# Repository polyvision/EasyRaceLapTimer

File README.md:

# EasyRaceLapTimer

EasyRaceLapTimer is a complete open source lap time tracker all-in-one solution for FPV racing quads. It supports an infrared based tracker solution which is completly open hardware and a VTX solution

What you get with EasyRaceLapTimer:

**Features:**

* host system for tracking the laps
* VTX sensoring
* IR transponders (code & schematic files for building them) with a transmitting range of 2 to 4 meters
* 63 available transponder IDs when using the project transponders
* changing the ID via a push button on the transponder, no additional programming required (started with version 0.3.1 of the transponders)
* update transponders with new code (Arduino hardware needed)
* setup guide for building your Raspberry PI host station
* the host station is also a WiFi access point to change configs etc on the fly
* monitoring mode, you can watch the stats with your mobile phones
* add your own team logo to the monitoring mode
* detailed stats about pilots and races
* sound effects for various events in a race
* TCP/IP and serial connections support for receiving lap times and commands from other time tracking systems
* export race events to PDF
* standard practice/ time trial mode
* competition mode for racing events with time penalties (satellites needed)
* automatic restarting of a race session after a specified idle time
* complete race management with heats & groups
* and much more comming soon

**Important notices**

EasyRaceLapTimer works basicly with any IR transponder, as long as you provide code for interpreting the IR pulses. Just have a look at the *ir_daemon* tool.

Be sure to use the full size of your SD card on the Raspberry PI

    sudo raspi-config

# Important information

The documentation for the project can be found in the [/docs](https://github.com/polyvision/EasyRaceLapTimer/tree/master/docs) directory.
There's also a huge [RCGroups](http://www.rcgroups.com/forums/showthread.php?t=2538917) thread with lots of answered questions, images etc.

# Version 0.6.x

You can download a SD card image for the PI of EasyRaceLapTimer on the following pages:

http://www.airbirds.de
http://www.easyracelaptimer.com

There's also an introduction video to the system.

# file structure

**/docs**
  documentation of nearly every part of the package

**/web**

the rails application

**/Arduino**

all arduino sketches

**/ir_daemon**

the cpp daemon for receiving the IR pulses

**/datasheets**

schematic files and more for transponders etc.

# Installation

fetch the source via git with the following command

    git clone git@github.com:polyvision/EasyRaceLapTimer.git

more details of each indivial package can be found in the *docs* folder

# Contributors
 * [Peter Provost](https://github.com/PProvost)
 * [Peisel](https://github.com/peisel)
 * [p3root](https://github.com/p3root)
 * [Sven Michel](https://github.com/svenmichel)
 * [bilson](https://github.com/bilson)
 
 and many more ! just add yourself if you contributed!

# license

The complete project uses the [GPL V3 license](http://www.gnu.org/licenses/gpl-3.0.de.html)

**development and sponsoring by [AirBirds](http://www.airbirds.de)**

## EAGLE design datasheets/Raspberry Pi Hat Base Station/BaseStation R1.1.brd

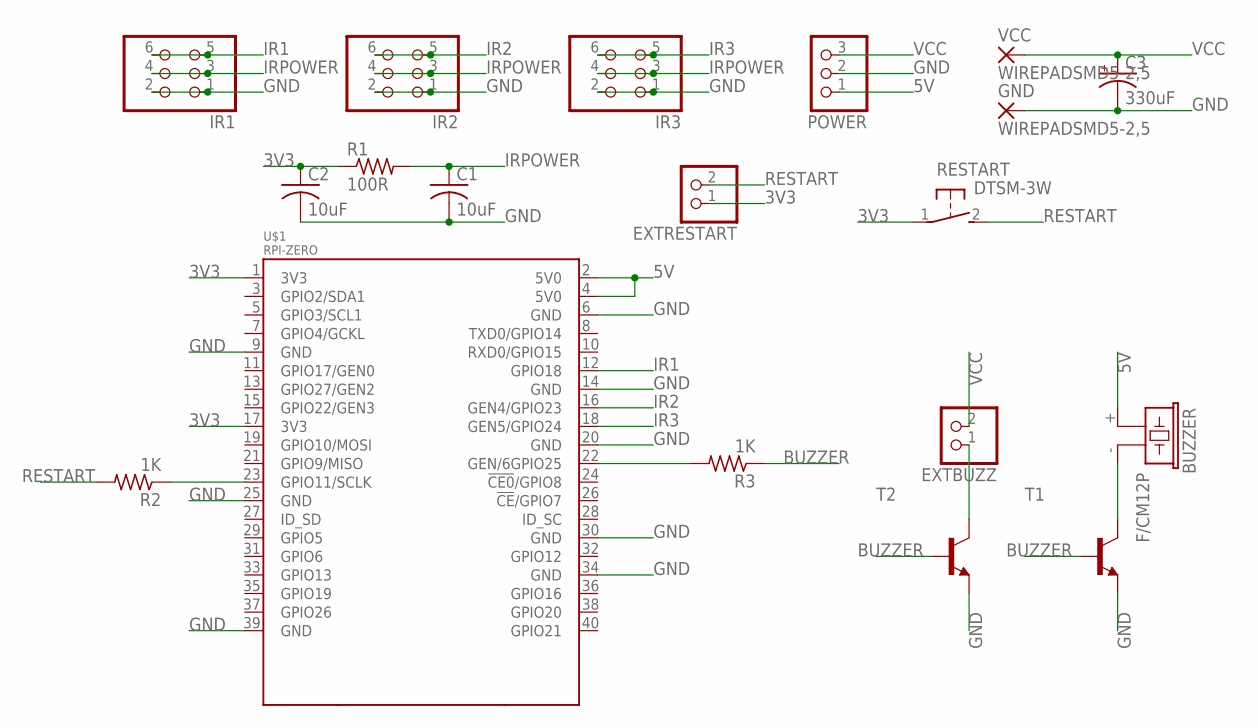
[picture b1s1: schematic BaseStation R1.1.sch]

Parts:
BUZZER: F/CM12P
C1, C2: 10uF; C1206K
C3: 330uF; E3,5-8
EXTBUZZ: PINHD-1X2; 1X02
EXTRESTART: PINHD-1X2; 1X02
GND: WIREPADSMD5-2,5; 5-2,5
IR1, IR2, IR3: PINHD-2X3; 2X03
POWER: PINHD-1X3; 1X03
R1: 100R; R1206W
R2, R3: 1K; R1206W
RESTART: DTSM-3W
T1, T2: MMBT2222ALT1-NPN-SOT23-BEC; SOT23-BEC
U$1: RPI-ZERO; RASPBERRYPI_BASTELSTUBE_V13_RASPI_BOARD_B+_FULL
VCC: WIREPADSMD5-2,5; 5-2,5

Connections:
3V3: C2.1, EXTRESTART.1, R1.1, RESTART.1, U$1.1 (3V3), U$1.17 (3V3)
5V: BUZZER.+ (1), POWER.1, U$1.2 (5V0), U$1.4 (5V0)
BUZZER: R3.1, T1.B, T2.B
GND: C1.2, C2.2, C3.-, GND.1, IR1.1, IR1.2, IR2.1, IR2.2, IR3.1, IR3.2, POWER.2, T1.E, T2.E, U$1.6 (GND), U$1.9 (GND), U$1.14 (GND), U$1.20 (GND), U$1.25 (GND), U$1.30 (GND), U$1.34 (GND), U$1.39 (GND)
IR1: IR1.5, IR1.6, U$1.12 (GPIO18)
IR2: IR2.5, IR2.6, U$1.16 (GEN4/GPIO23)
IR3: IR3.5, IR3.6, U$1.18 (GEN5/GPIO24)
IRPOWER: C1.1, IR1.3, IR1.4, IR2.3, IR2.4, IR3.3, IR3.4, R1.2
unnamed: R2.1, U$1.23 (GPIO11/SCLK)
unnamed: R3.2, U$1.22 (GEN/6GPIO25)
unnamed: BUZZER.- (2), T1.C
unnamed: EXTBUZZ.1, T2.C
RESTART: EXTRESTART.2, R2.2, RESTART.2
VCC: C3.+, EXTBUZZ.2, POWER.3, VCC.1

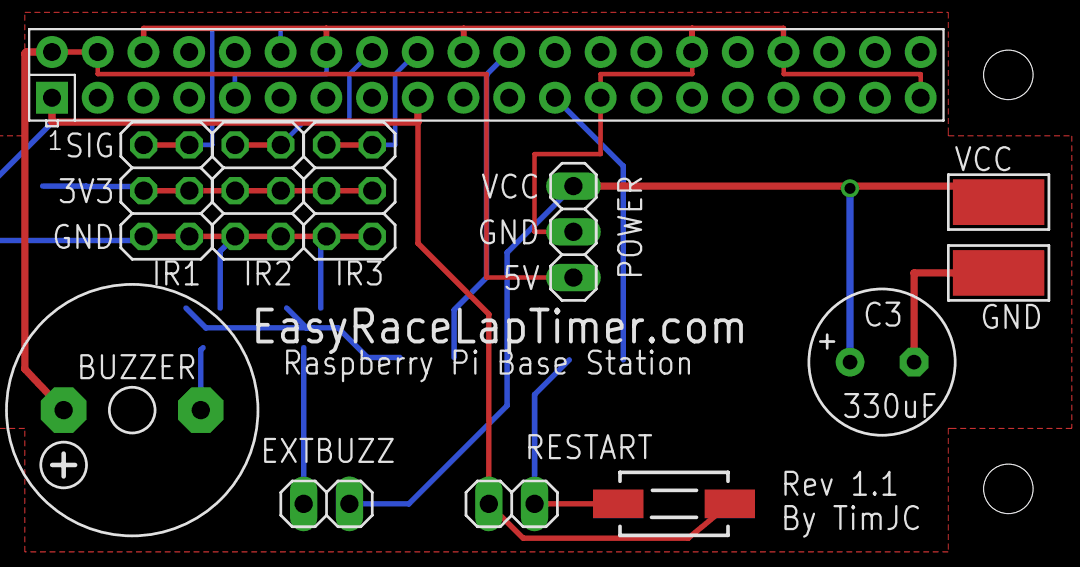
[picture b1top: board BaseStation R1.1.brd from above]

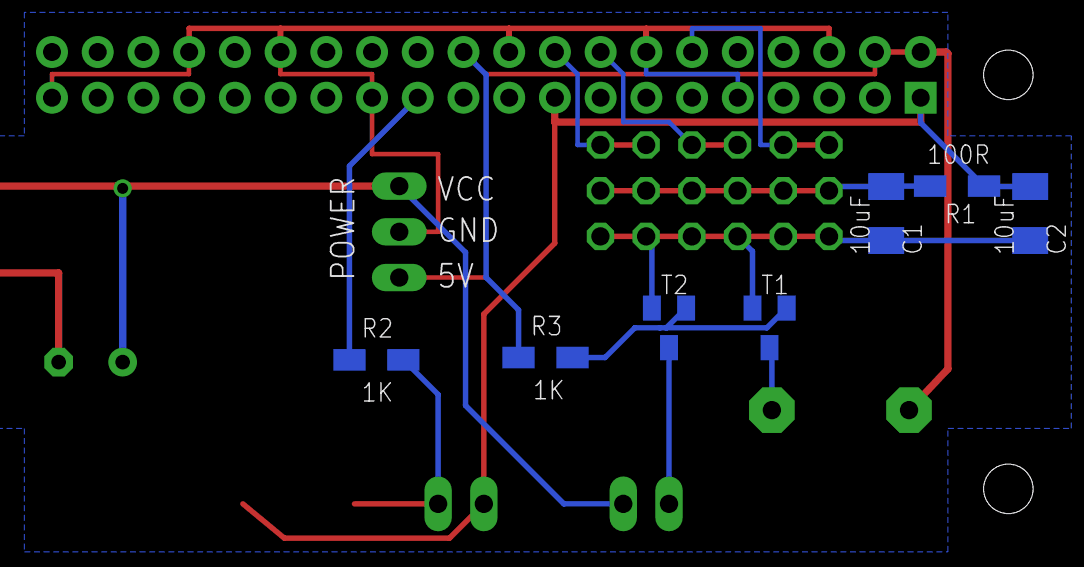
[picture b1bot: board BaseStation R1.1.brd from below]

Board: 2 copper layers, 19 parts (7 on the bottom side), 14 nets.

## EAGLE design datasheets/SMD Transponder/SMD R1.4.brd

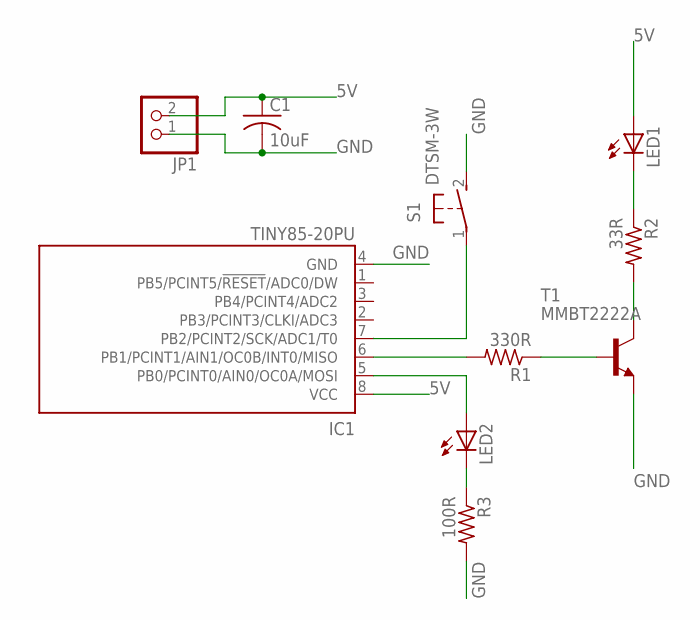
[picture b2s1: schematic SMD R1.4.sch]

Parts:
C1: 10uF; C1206K
IC1: TINY85-20PU; 8S2
JP1: PINHD-1X2; 1X02
LED1: LED5MM
LED2: LEDSML1206; SML1206
R1: 330R; R1206W
R2: 33R; R1206W
R3: 100R; R1206W
S1: DTSM-3W
T1: MMBT2222A; SOT23-BEC

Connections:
5V: C1.1, IC1.8 (VCC), JP1.2, LED1.A
GND: C1.2, IC1.4 (GND), JP1.1, R3.2, S1.2, T1.E
unnamed: IC1.5 (PB0/PCINT0/AIN0/OC0A/MOSI), LED2.A
unnamed: LED1.K (C), R2.1
unnamed: R2.2, T1.C
unnamed: R1.1, T1.B
unnamed: IC1.6 (PB1/PCINT1/AIN1/OC0B/INT0/MISO), R1.2
unnamed: LED2.C, R3.1
unnamed: IC1.7 (PB2/PCINT2/SCK/ADC1/T0), S1.1

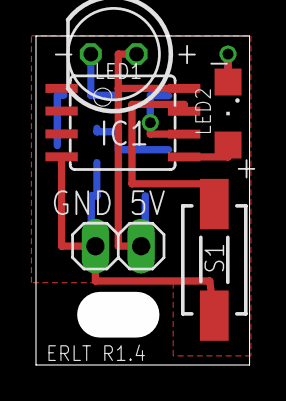
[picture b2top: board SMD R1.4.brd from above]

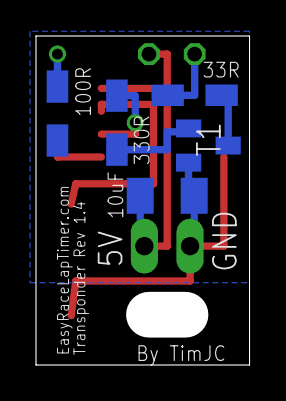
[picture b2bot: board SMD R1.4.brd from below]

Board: 2 copper layers, 11.9 x 18.3 mm, 10 parts (5 on the bottom side), 9 nets.

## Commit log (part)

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2015-11-03 first working version of receiver
2015-11-04 new file strucure
2015-11-04 added some docs
2015-11-06 updated docs
2015-11-08 3 sensor support added buzzer support
2015-11-08 added gpio wiring for raspberry2
2015-11-09 added hardware.md
2015-11-10 added missing part
2015-11-13 added database config for production mode
2015-11-13 added pilots views, bugfixes
2015-11-13 fixes
2015-11-13 websockets r now configurable via env variable RAILS_CABLE_IP
2015-11-13 added init.d script
2015-11-14 added new style, added check for too fast lap
2015-11-16 preparing first stable release
2015-11-17 changed ir_daemon to 9 bit mode POST requests in seperate threads
2015-11-17 added Arduino files for the new 9bit transponder docs updated etc
2015-11-18 added missing transponder setup file
2015-11-18 added blog post link
2015-11-19 added soundfile configuration
2015-11-19 changed checksum calculation according to the documentation
2015-11-19 changed checksum calculation -> added new Transponder code v0.2
2015-11-20 better documentation
2015-11-20 updated documentation
2015-11-20 fixed a bug in displaying last rounds wrong time
2015-11-23 added api testing new config value lap_max_lap_time_in_seconds
2015-11-23 added database cleaner gem
2015-11-23 added button support on PIN 14 to start a new race started to clean up ir_daemon code
2015-11-24 rewrite of ir_daemon to support additionaly TCP/IP and serial connections
2015-11-24 Update setup_guide.md
    Made a bunch of edits and clarifications to help new users.
2015-11-26 added file
2015-11-27 better ui
2015-11-27 upcomming v0.3 added sensor case for different direction started to write update instructions, not complete yet
2015-11-30 wip competition mode
2015-12-01 first working version of the competition mode
2015-12-02 displayotron 3000 HAT server
2015-12-02 added lcd support (Displayotron 3000 HAT) support by adding an info server added more config switches to the ir_daemon
2015-12-04 beginning of satellite mode and time penalties for competition mode
2015-12-06 fixed competition mode ranking beginning of pdf generation
2015-12-06 add arch-linux description
2015-12-07 fixed a bug with double using transponder tokens
2015-12-07 satellite mode for the ir_daemon
2015-12-08 various bug fixes
2015-12-10 added version info the gui fixex image bug in pdf export
2015-12-10 - refactoring - added logging class for syslog and console logging (file is todo) - possibility to add more ir sensors via config file
2015-12-10 removed readme file
2015-12-10 updated testing code for Arduino Nano
2015-12-18 monitor view updates all 2 seconds removed actioncable
2015-12-18 changed config values
2015-12-18 first implementation of hot seat mode
2015-12-19 fixed spelling
2015-12-19 fixed a bug regarding hot seat mode in competition mode added spec for hot seat mode
2015-12-21 added udp broadcast, first tests
2015-12-22 fixes for upcomming v0.4b2
2015-12-22 fix for button visibility
2015-12-22 button visibility
2015-12-23 fixed typos and updated docs
2015-12-24 personal best lap time sfx
2015-12-24 fix for resetting the ir_daemon
2015-12-25 added sidekiq for background processing
2015-12-25 Use existing INI file and settings if exists
2016-01-04 test
2016-01-05 new colors new feeling more racy
2016-01-06 css fix
2016-01-11 working volume control
2016-01-11 playing custom sound files from via race director
2016-01-17 first working version of race director in the web gui improved some things and fixed a couple of bugs in ir_daemon
2016-01-17 fixes regarding logging
2016-01-22 fixed bug with creating a race session
2016-01-26 wip...
2016-01-29 play sound files for each lap in competition mode
2016-01-30 working playing lap num sound for a pilot in standard racing mode
2016-01-31 work in progress for sound effects during a race
2016-01-31 added docs notice
2016-02-01 working auto restart, option is called idle_time_in_seconds... let's test this on the field
2016-02-01 fixed a logic bomb ;)
2016-02-01 updated doc
2016-02-08 make the datasheet path a clickable link
2016-02-14 Kicad transmitter circuit and PCB
2016-02-16 Revert "Kicad PCB layout"
    This reverts commit 9afb40ae9a6d2ea0d6b4d8b9758429dc2c52fee4.
2016-02-16 Revert "Kicad transmitter circuit and PCB"
    This reverts commit 51ba06ca087ca7753eddb7d80b7d77b9e4b8eb6c.
2016-02-17 Add wiringpi to the list of required packages before building ir_daemon
2016-02-28 logo fix
2016-03-03 changed versioning
2016-03-05 IR Daemon v2 initial commit
2016-03-06 added transmitter code rev 0.3.1
2016-03-06 added rake task
2016-03-08 Convert to IO::Async
2016-03-10 Filter duplicate codes sent in short timespan
2016-03-13 Add header pulse/space of 1200 microseconds
2016-03-13 Switch for going between v0.3 (or lower) protocol or the newer version
2016-03-13 Correct handling of the checksum
2016-03-13 Document v.4 protocol, and move old protocol docs into an old file
2016-03-13 Correct note about clock rate
2016-03-15 IR sensor mount
    Alternative 3D printed IR receiver mount for TSOP31238. These are designed to mounted to the back side of agate with 1/4" or 5-6mm wide zip ties. The TSOP is held in the mount with double sided foam 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
2016-03-15 PCB Files for SMD Transponder and Pi Hat Base Station
2016-03-17 Add documentation
2016-03-18 [Invalidate Lap] Add "Invalidated" field and handle it in queries
2016-03-18 [Invalidate Lap] Basic UI to mark laps as invalid
2016-03-22 Send lap time to web server
2016-03-31 Reroute LED and transistor. Remove backup files from git.
2016-04-01 Adding screenshot of Pi Hat Base Station schematic
2016-04-06 Replace 3 blink startup with transponder id
    replace the 3 blink startup with two sets of blinks (with a blink in between) to display the MSB and LSB of the transponder ID. for example 21 will be displayed as 2 quick blinks, a separating blink,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
2016-04-09 fix bug with trasponder id flash on setup hanging
2016-04-09 flash transponder id each time trasponder id is changed
2016-04-12 Editing component list
    Added TSUS5202 as additional example of IR LED
    Changed 56 Ohm resistor to 33 Ohm for increased LED output.
    Added Edimax EW-7811Un as example USB WiFi adapter
2016-04-15 Fixed broken link for Transponder 0.3.1 schematic
2016-04-15 Add -bak to list of ignored files to catch a few kicad backup files
2016-04-29 Script to set transponder code via avrdude
2016-05-03 fixed specs
2016-05-04 incorrect pulses
    3rd bit should be a pulse rather than a space
2016-05-06 Updated setup_guide.md Added instructions to connect to the website
2016-05-09 Fixed typo in setup_guide.md "chmod +x" was missing a space
2016-05-12 Removed duplicate redis-server in apt-get command
2016-05-18 interface_guide.md v0.1
    A small guide for the ERLT interface
2016-05-20 Troubleshooting sidekiq startup
    Added section for troubleshooting issues with sidekiq not running on boot.
2016-05-20 Formatting changes
    Formatted the `code` sections of troubleshooting sound effects playback
2016-05-20 Cleaning up formatting
    I screwed up the code formatting and the back-ticks were visible.
2016-05-20 updated documentation
    added missing space in wkhtmltopdf permission set command
2016-06-02 first version with VTX sensoring support
2016-07-12 added missing brackets
2016-07-12 to clone the 0.6 branch
2016-08-01 migrated to rails 5, removed sqlite and switched to mysql as a database engine
2016-08-02 continued working on race events
2016-08-04 worked on basic race event flow starting race sessions via race event group, works ;)
2016-08-04 added ruby version file
2016-08-04 adjusted ruby version
2016-08-04 fixed tests,
    at present, spec/adapters/race_event_race_session_builder_adapter_spec.rb works runned alone, with all other tests together not... but why?
2016-08-05 added mode for regrouping a heat based on previous heat pilot placements
2016-08-05 improvements for race event managent in the GUI
2016-08-07 added the possibility to move pilots from one group to another
2016-08-08 fixed a bug in next heat calculation
2016-08-24 added pilot json data to monitor api
2016-08-24 beginning of ir_daemon2 based on nodejs thanks to Rodrigo Pérez for the base code of the vtx sensor
2016-08-25 added import of pilots from fpv-sports.io y:
2016-08-25 added validation & invalidation to history
2016-08-30 added possibility to merge lap times of a pilot
2016-08-31 added support for the RaceBox (upcomming Raspbery PI OpenSource HAT) for easier connecting the PocketEdition and other VTX systems
2016-08-31 removed monitor polling in favour of actioncable (websockets)
2016-09-01 improved information
2016-09-02 added actioncable to race box config
2016-09-02 updated docs, small fixes
2016-09-05 first working implementation with fpv-sports.io support
2016-09-07 added invalidating laps in monitor
2016-09-07 a few more changes
2016-09-29 fix for getting data from fpv-sports.io
2016-09-29 wip ir decoding via nodejs
2017-03-23 Update wifi.md
    The password in the Setup Guide differs from the original password here. Updating it to reduce confusion.
2017-07-30 fixes missing url
2017-07-30 adds mac friendly tool to docs
2017-07-31 fix lap_track response on standard mode
2021-02-18 Updated to rails 4.2.11.3 to run on modern systems
2021-02-25 Updated dependencies
2021-02-27 Updated webpack output
2021-02-28 Bump superagent from 1.8.5 to 3.7.0 in /web
    Bumps [superagent](https://github.com/visionmedia/superagent) from 1.8.5 to 3.7.0.
    - [Release notes](https://github.com/visionmedia/superagent/releases)
    - [Changelog](https://github.com/visionmedia/superagent/blob/master/HISTORY.md)
    - [Commits](https://github.com/visionmedia/superagent/commits/v3.7.0)
2021-02-28 Bump node-fetch from 1.7.3 to 2.6.1 in /web
    Bumps [node-fetch](https://github.com/bitinn/node-fetch) from 1.7.3 to 2.6.1.
    - [Release notes](https://github.com/bitinn/node-fetch/releases)
    - [Changelog](https://github.com/node-fetch/node-fetch/blob/master/docs/CHANGELOG.md)
    - [Commits](https://github.com/bitinn/node-fetch/compare/1.7.3...v2.6.1)
2021-05-12 Bump lodash from 3.10.1 to 4.17.21 in /web
    Bumps [lodash](https://github.com/lodash/lodash) from 3.10.1 to 4.17.21.
    - [Release notes](https://github.com/lodash/lodash/releases)
    - [Commits](https://github.com/lodash/lodash/compare/3.10.1...4.17.21)
2022-01-22 Bump node-fetch from 1.7.3 to 3.1.1 in /web
    Bumps [node-fetch](https://github.com/node-fetch/node-fetch) from 1.7.3 to 3.1.1.
    - [Release notes](https://github.com/node-fetch/node-fetch/releases)
    - [Changelog](https://github.com/node-fetch/node-fetch/blob/main/docs/CHANGELOG.md)
    - [Commits](https://github.com/node-fetch/node-fetch/compare/1.7.3...v3.1.1)
    ---
    updated-dependencies:
2022-11-01 Bump minimatch and babel-loader in /web
    Bumps [minimatch](https://github.com/isaacs/minimatch) to 3.1.2 and updates ancestor dependency [babel-loader](https://github.com/babel/babel-loader). These dependencies need to be updated together.
    Updates `minimatch` from 2.0.10 to 3.1.2
    - [Release notes](https://github.com/isaacs/minimatch/releases)
    - [Commits](https://github.com/isaacs/minimatch/compare/v2.0.10...v3.1.2)
    Updates `babel-loader` from 5.4.2 to 9.0.1
    - [Release notes](https://github.com/babel/babel-loader/releases)
2022-12-06 Bump qs and superagent in /web
    Bumps [qs](https://github.com/ljharb/qs) to 6.11.0 and updates ancestor dependency [superagent](https://github.com/ladjs/superagent). These dependencies need to be updated together.
    Updates `qs` from 2.3.3 to 6.11.0
    - [Release notes](https://github.com/ljharb/qs/releases)
    - [Changelog](https://github.com/ljharb/qs/blob/main/CHANGELOG.md)
    - [Commits](https://github.com/ljharb/qs/compare/v2.3.3...v6.11.0)
    Updates `superagent` from 1.8.5 to 8.0.5
